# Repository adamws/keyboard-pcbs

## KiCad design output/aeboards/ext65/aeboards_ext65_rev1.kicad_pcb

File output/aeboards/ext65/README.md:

## aeboards/ext65/aeboards_ext65_rev1

[layout](aeboards_ext65_rev1-kle.json) - [PCB](aeboards_ext65_rev1.kicad_pcb)

{:loading="lazy"}

[Open in keyboard-layout-editor](http://www.keyboard-layout-editor.com/##@@_x:1.25&y:1.25&c=#aaaaaa;&=0,0&=1,0&=0,1&=1,1&_x:0.5&c=#888888;&=0,2&_c=#cccccc;&=1,2&=0,3&=1,3&=0,4&=1,4&=0,5&=1,5&=0,6&=1,6&=0,7&=1,7&=0,8&_c=#aaaaaa&w:2;&=1,8%0A%0A%0A0,0&=0,9;&@_x:1.25&h:2;&=4,0%0A%0A%0A1,0&_c=#cccccc;&=3,0&=2,1&=3,1&_x:0.5&c=#aaaaaa&w:1.5;&=2,2&_c=#cccccc;&=3,2&=2,3&=3,3&=2,4&=3,4&=2,5&=3,5&=2,6&=3,6&=2,7&=3,7&=2,8&_w:1.5;&=3,8&_c=#aaaaaa;&=2,9;&@_x:2.25&c=#cccccc;&=5,0&=4,1&=5,1&_x:0.5&c=#aaaaaa&w:1.75;&=4,2&_c=#cccccc;&=5,2&=4,3&=5,3&=4,4&=5,4&=4,5&=5,5&=4,6&=5,6&=4,7&=5,7&_c=#aaaaaa&w:2.25;&=4,8&=4,9;&@_x:1.25&h:2;&=8,0%0A%0A%0A2,0&_c=#cccccc;&=7,0&=6,1&=7,1&_x:0.5&c=#aaaaaa&w:2.25;&=6,2&_c=#cccccc;&=7,2&=6,3&=7,3&=6,4&=7,4&=6,5&=7,5&=6,6&=7,6&=6,7&_c=#aaaaaa&w:1.75;&=7,8&_c=#888888;&=6,8&_c=#aaaaaa;&=7,9;&@_x:2.25&c=#cccccc;&=9,0&_w:2;&=9,1%0A%0A%0A3,0&_x:0.5&c=#aaaaaa&w:1.5;&=8,2&=9,2&_w:1.5;&=8,3&_c=#cccccc&w:6.25;&=8,5&_c=#aaaaaa&w:1.25;&=9,6&=8,7&_x:0.5&c=#888888;&=9,8&=8,8&=9,9;&@_x:18.75&y:-6.25&c=#cccccc;&=1,8%0A%0A%0A0,1&=5,8%0A%0A%0A0,1;&@_y:1.25&c=#aaaaaa;&=2,0%0A%0A%0A1,1;&@=4,0%0A%0A%0A1,1;&@=6,0%0A%0A%0A2,1;&@=8,0%0A%0A%0A2,1;&@_x:3.25&y:0.25&c=#cccccc;&=8,1%0A%0A%0A3,1&=9,1%0A%0A%0A3,1)

{:loading="lazy"}

## aeboards/ext65/aeboards_ext65_rev2

[layout](aeboards_ext65_rev2-kle.json) - [PCB](aeboards_ext65_rev2.kicad_pcb)

{:loading="lazy"}

[Open in keyboard-layout-editor](http://www.keyboard-layout-editor.com/##@@_x:1.25&y:1.25&c=#aaaaaa;&=0,0&=1,0&=0,1&=1,1&_x:0.5&c=#888888;&=0,2&_c=#cccccc;&=1,2&=0,3&=1,3&=0,4&=1,4&=0,5&=1,5&=0,6&=1,6&=0,7&=1,7&=0,8&_c=#aaaaaa&w:2;&=1,8%0A%0A%0A0,0&=0,9;&@_x:1.25&h:2;&=4,0%0A%0A%0A1,0&_c=#cccccc;&=3,0&=2,1&=3,1&_x:0.5&c=#aaaaaa&w:1.5;&=2,2&_c=#cccccc;&=3,2&=2,3&=3,3&=2,4&=3,4&=2,5&=3,5&=2,6&=3,6&=2,7&=3,7&=2,8&_w:1.5;&=3,8&_c=#aaaaaa;&=2,9;&@_x:2.25&c=#cccccc;&=5,0&=4,1&=5,1&_x:0.5&c=#aaaaaa&w:1.75;&=4,2&_c=#cccccc;&=5,2&=4,3&=5,3&=4,4&=5,4&=4,5&=5,5&=4,6&=5,6&=4,7&=5,7&_c=#aaaaaa&w:2.25;&=4,8&=4,9;&@_x:1.25&h:2;&=8,0%0A%0A%0A2,0&_c=#cccccc;&=7,0&=6,1&=7,1&_x:0.5&c=#aaaaaa&w:2.25;&=6,2&_c=#cccccc;&=7,2&=6,3&=7,3&=6,4&=7,4&=6,5&=7,5&=6,6&=7,6&=6,7&_c=#aaaaaa&w:1.75;&=7,8&_c=#888888;&=6,8&_c=#aaaaaa;&=7,9;&@_x:2.25&c=#cccccc;&=9,0&_w:2;&=9,1%0A%0A%0A3,0&_x:0.5&c=#aaaaaa&w:1.5;&=8,2&=9,2&_w:1.5;&=8,3&_c=#cccccc&w:6.25;&=8,5&_c=#aaaaaa&w:1.25;&=9,6&=8,7&_x:0.5&c=#888888;&=9,8&=8,8&=9,9;&@_x:18.75&y:-6.25&c=#cccccc;&=1,8%0A%0A%0A0,1&=5,8%0A%0A%0A0,1;&@_y:1.25&c=#aaaaaa;&=2,0%0A%0A%0A1,1;&@=4,0%0A%0A%0A1,1;&@=6,0%0A%0A%0A2,1;&@=8,0%0A%0A%0A2,1;&@_x:3.25&y:0.25&c=#cccccc;&=8,1%0A%0A%0A3,1&=9,1%0A%0A%0A3,1)

{:loading="lazy"}

## aeboards/ext65/aeboards_ext65_rev3

[layout](aeboards_ext65_rev3-kle.json) - [PCB](aeboards_ext65_rev3.kicad_pcb)

{:loading="lazy"}

[Open in keyboard-layout-editor](http://www.keyboard-layout-editor.com/##@@_c=#aaaaaa;&=0,0&=1,0&=0,1&=1,1&_x:0.5&c=#888888;&=0,2&_c=#cccccc;&=1,2&=0,3&=1,3&=0,4&=1,4&=0,5&=1,5&=0,6&=1,6&=0,7&=1,7&=0,8&_c=#aaaaaa&w:2;&=1,8&=0,9;&@_h:2;&=2,0&_c=#cccccc;&=3,0&=2,1&=3,1&_x:0.5&c=#aaaaaa&w:1.5;&=2,2&_c=#cccccc;&=3,2&=2,3&=3,3&=2,4&=3,4&=2,5&=3,5&=2,6&=3,6&=2,7&=3,7&=2,8&_w:1.5;&=3,8&_c=#aaaaaa;&=2,9;&@_x:1&c=#cccccc;&=5,0&=4,1&=5,1&_x:0.5&c=#aaaaaa&w:1.75;&=4,2&_c=#cccccc;&=5,2&=4,3&=5,3&=4,4&=5,4&=4,5&=5,5&=4,6&=5,6&=4,7&=5,7&_c=#aaaaaa&w:2.25;&=4,8&=4,9;&@_h:2;&=6,0&_c=#cccccc;&=7,0&=6,1&=7,1&_x:0.5&c=#aaaaaa&w:2.25;&=6,2&_c=#cccccc;&=7,2&=6,3&=7,3&=6,4&=7,4&=6,5&=7,5&=6,6&=7,6&=6,7&_c=#aaaaaa&w:1.75;&=7,8&_c=#888888;&=6,8&_c=#aaaaaa;&=7,9;&@_x:1&c=#cccccc;&=9,0&_w:2;&=8,1&_x:0.5&c=#aaaaaa&w:1.25;&=8,2&_w:1.25;&=9,2&_w:1.25;&=8,3&_c=#cccccc&w:6.25;&=8,5&_c=#aaaaaa&w:1.5;&=9,6&_w:1.5;&=8,7&_c=#888888;&=9,8&=8,8&=9,9)

{:loading="lazy"}

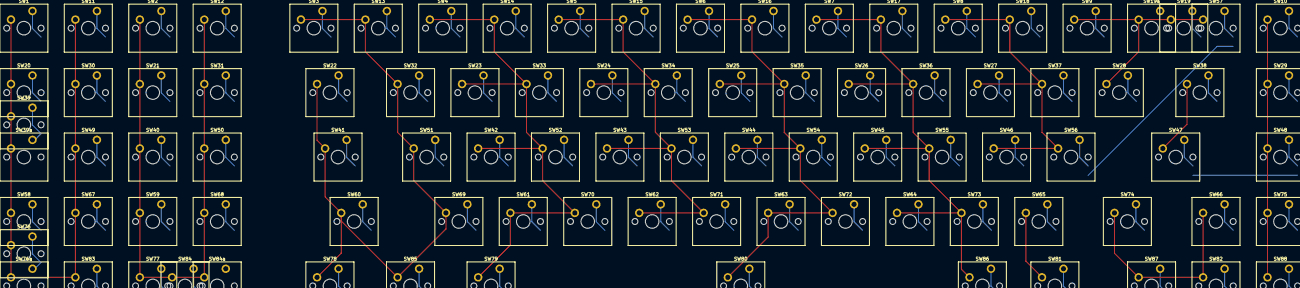
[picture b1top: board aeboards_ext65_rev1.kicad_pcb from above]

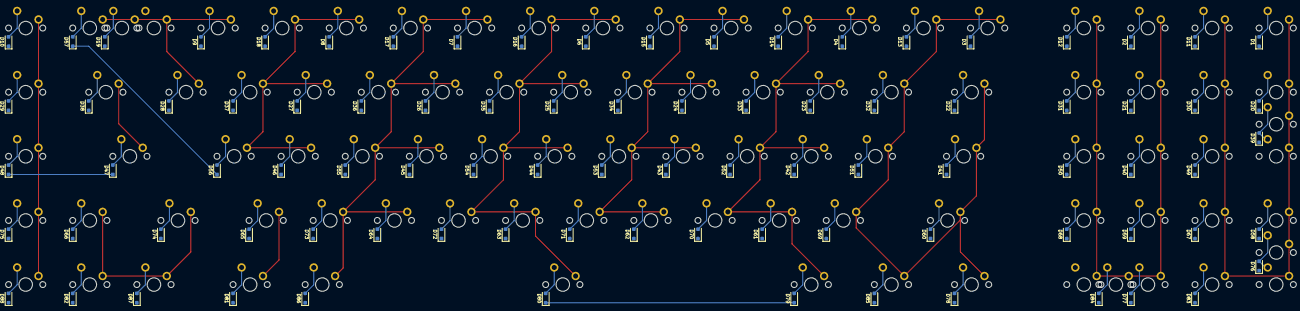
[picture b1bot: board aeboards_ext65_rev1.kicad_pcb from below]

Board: 2 copper layers, 180 parts (88 on the bottom side), 108 nets.

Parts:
D1, D2, D3, D4, D5, D6, D7, D8, D9, D10, D11, D12, D13, D14, D15, D16, D17, D18, D19, D20, D21, D22, D23, D24, D25, D26, D27, D28, D29, D30, D31, D32, D33, D34, D35, D36, D37, D38, D39, D40, D41, D42, D43, D44, D45, D46, D47, D48, D49, D50, D51, D52, D53, D54, D55, D56, D57, D58, D59, D60, D61, D62, D63, D64, D65, D66, D67, D68, D69, D70, D71, D72, D73, D74, D75, D76, D77, D78, D79, D80, D81, D82, D83, D84, D85, D86, D87, D88: D_SOD-123F
SW1, SW2, SW3, SW4, SW5, SW6, SW7, SW8, SW9, SW10, SW11, SW12, SW13, SW14, SW15, SW16, SW17, SW18, SW19, SW19a, SW20, SW21, SW22, SW23, SW24, SW25, SW26, SW27, SW28, SW29, SW30, SW31, SW32, SW33, SW34, SW35, SW36, SW37, SW38, SW39, SW39a, SW40, SW41, SW42, SW43, SW44, SW45, SW46, SW47, SW48, SW49, SW50, SW51, SW52, SW53, SW54, SW55, SW56, SW57, SW58, SW59, SW60, SW61, SW62, SW63, SW64, SW65, SW66, SW67, SW68, SW69, SW70, SW71, SW72, SW73, SW74, SW75, SW76, SW76a, SW77, SW78, SW79, SW80, SW81, SW82, SW83, SW84, SW84a, SW85, SW86, SW87, SW88: SW_Cherry_MX_PCB_1.00u

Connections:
COL0: SW1.1, SW11.1, SW20.1, SW30.1, SW39.1, SW39a.1, SW49.1, SW58.1, SW67.1, SW76.1, SW76a.1, SW83.1
COL1: SW2.1, SW12.1, SW21.1, SW31.1, SW40.1, SW50.1, SW59.1, SW68.1, SW77.1, SW84.1, SW84a.1
COL2: SW3.1, SW13.1, SW22.1, SW32.1, SW41.1, SW51.1, SW60.1, SW69.1, SW78.1, SW85.1
COL3: SW4.1, SW14.1, SW23.1, SW33.1, SW42.1, SW52.1, SW61.1, SW70.1, SW79.1
COL4: SW5.1, SW15.1, SW24.1, SW34.1, SW43.1, SW53.1, SW62.1, SW71.1
COL5: SW6.1, SW16.1, SW25.1, SW35.1, SW44.1, SW54.1, SW63.1, SW72.1, SW80.1
COL6: SW7.1, SW17.1, SW26.1, SW36.1, SW45.1, SW55.1, SW64.1, SW73.1, SW86.1
COL7: SW8.1, SW18.1, SW27.1, SW37.1, SW46.1, SW56.1, SW65.1, SW81.1
COL8: SW9.1, SW19.1, SW19a.1, SW28.1, SW38.1, SW47.1, SW57.1, SW66.1, SW74.1, SW82.1, SW87.1
COL9: SW10.1, SW29.1, SW48.1, SW75.1, SW88.1
unnamed: D1.2, SW1.2
unnamed: D2.2, SW2.2
unnamed: D3.2, SW3.2
unnamed: D4.2, SW4.2
unnamed: D5.2, SW5.2
unnamed: D6.2, SW6.2
unnamed: D7.2, SW7.2
unnamed: D8.2, SW8.2
unnamed: D9.2, SW9.2
unnamed: D10.2, SW10.2
unnamed: D11.2, SW11.2
unnamed: D12.2, SW12.2
unnamed: D13.2, SW13.2
unnamed: D14.2, SW14.2
unnamed: D15.2, SW15.2
unnamed: D16.2, SW16.2
unnamed: D17.2, SW17.2
unnamed: D18.2, SW18.2
unnamed: D19.2, SW19.2, SW19a.2
unnamed: D20.2, SW20.2
unnamed: D21.2, SW21.2
unnamed: D22.2, SW22.2
unnamed: D23.2, SW23.2
unnamed: D24.2, SW24.2
unnamed: D25.2, SW25.2
unnamed: D26.2, SW26.2
unnamed: D27.2, SW27.2
unnamed: D28.2, SW28.2
unnamed: D29.2, SW29.2
unnamed: D30.2, SW30.2
unnamed: D31.2, SW31.2
unnamed: D32.2, SW32.2
unnamed: D33.2, SW33.2
unnamed: D34.2, SW34.2
unnamed: D35.2, SW35.2
unnamed: D36.2, SW36.2
unnamed: D37.2, SW37.2
unnamed: D38.2, SW38.2
unnamed: D39.2, SW39.2, SW39a.2
unnamed: D40.2, SW40.2
unnamed: D41.2, SW41.2
unnamed: D42.2, SW42.2
unnamed: D43.2, SW43.2
unnamed: D44.2, SW44.2
unnamed: D45.2, SW45.2
unnamed: D46.2, SW46.2
unnamed: D47.2, SW47.2
unnamed: D48.2, SW48.2
unnamed: D49.2, SW49.2
unnamed: D50.2, SW50.2
unnamed: D51.2, SW51.2
unnamed: D52.2, SW52.2
unnamed: D53.2, SW53.2
unnamed: D54.2, SW54.2
unnamed: D55.2, SW55.2
unnamed: D56.2, SW56.2
unnamed: D57.2, SW57.2
unnamed: D58.2, SW58.2
unnamed: D59.2, SW59.2
unnamed: D60.2, SW60.2
unnamed: D61.2, SW61.2
unnamed: D62.2, SW62.2
unnamed: D63.2, SW63.2
unnamed: D64.2, SW64.2
unnamed: D65.2, SW65.2
unnamed: D66.2, SW66.2
unnamed: D67.2, SW67.2
unnamed: D68.2, SW68.2
unnamed: D69.2, SW69.2
unnamed: D70.2, SW70.2
unnamed: D71.2, SW71.2
unnamed: D72.2, SW72.2
unnamed: D73.2, SW73.2
unnamed: D74.2, SW74.2
unnamed: D75.2, SW75.2
unnamed: D76.2, SW76.2, SW76a.2
unnamed: D77.2, SW77.2
unnamed: D78.2, SW78.2
unnamed: D79.2, SW79.2
unnamed: D80.2, SW80.2
unnamed: D81.2, SW81.2
unnamed: D82.2, SW82.2
unnamed: D83.2, SW83.2
unnamed: D84.2, SW84.2, SW84a.2
unnamed: D85.2, SW85.2
unnamed: D86.2, SW86.2
unnamed: D87.2, SW87.2
unnamed: D88.2, SW88.2
ROW0: D1.1, D2.1, D3.1, D4.1, D5.1, D6.1, D7.1, D8.1, D9.1, D10.1
ROW1: D11.1, D12.1, D13.1, D14.1, D15.1, D16.1, D17.1, D18.1, D19.1
ROW2: D20.1, D21.1, D22.1, D23.1, D24.1, D25.1, D26.1, D27.1, D28.1, D29.1
ROW3: D30.1, D31.1, D32.1, D33.1, D34.1, D35.1, D36.1, D37.1, D38.1
ROW4: D39.1, D40.1, D41.1, D42.1, D43.1, D44.1, D45.1, D46.1, D47.1, D48.1
ROW5: D49.1, D50.1, D51.1, D52.1, D53.1, D54.1, D55.1, D56.1, D57.1
ROW6: D58.1, D59.1, D60.1, D61.1, D62.1, D63.1, D64.1, D65.1, D66.1
ROW7: D67.1, D68.1, D69.1, D70.1, D71.1, D72.1, D73.1, D74.1, D75.1
ROW8: D76.1, D77.1, D78.1, D79.1, D80.1, D81.1, D82.1
ROW9: D83.1, D84.1, D85.1, D86.1, D87.1, D88.1
